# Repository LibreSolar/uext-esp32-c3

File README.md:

# WiFi/Bluetooth communication board based on ESP32-C3 for UEXT connector

 First boards tested, some issues might still be open.

Schematic: [PDF file](build/uext-esp32-c3.pdf)

Bill of Materials: [CSV file](build/uext-esp32-c3_bom.csv) or [interactive HTML BOM](https://libre.solar/uext-esp32-c3/build/uext-esp32-c3_ibom.html)

## Features

- UEXT connector to communicate with host MCU via UART
- Flashing via built-in USB port
- Internal power supply for firmware upgrades

## Firmware

This board can be programmed with [Zephyr RTOS](https://docs.zephyrproject.org/latest/) or [ESP-IDF](https://docs.espressif.com/projects/esp-idf/en/latest/esp32c3/get-started/index.html).

## License

The hardware is licensed under the [CERN Open Hardware Licence Version 2 - Weakly Reciprocal](LICENCE).

Documentation is licensed under the [Creative Commons Attribution-ShareAlike 4.0 International (CC BY-SA 4.0) License](https://creativecommons.org/licenses/by-sa/4.0/).

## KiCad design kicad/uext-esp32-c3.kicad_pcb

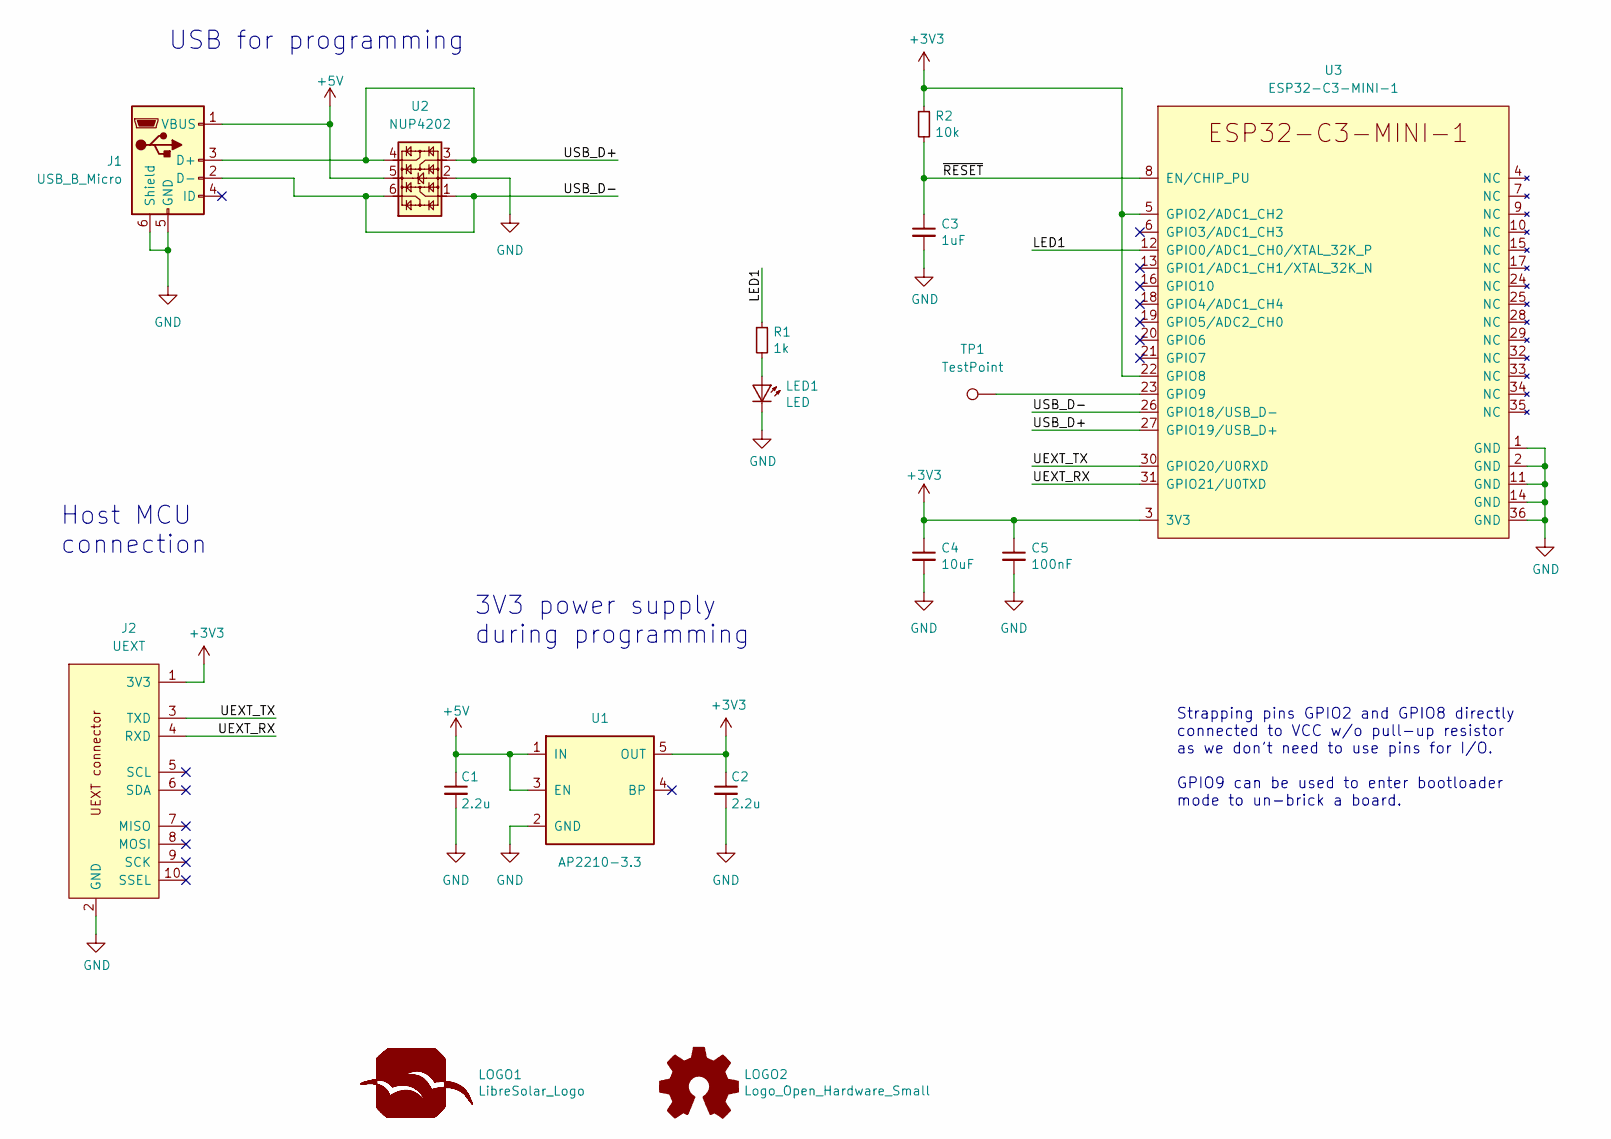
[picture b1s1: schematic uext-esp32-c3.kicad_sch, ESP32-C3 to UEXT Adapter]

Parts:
C1, C2: 2.2u; C_0603_1608
C3: 1uF; C_0603_1608
C4: 10uF; C_0805_2012
C5: 100nF; C_0603_1608
J1: USB_B_Micro; USB_Micro-B_10103594-0001LF; PartNumber 10103594-0001LF
J2: UEXT; PinSocket_2x05_P2.54mm_Vertical
LED1: LED; LED_0603_1608Metric; PartNumber red
LOGO1: LibreSolar_Logo; LIBRESOLAR_LOGO
LOGO2: Logo_Open_Hardware_Small; OSHW-Logo_5.7x6mm_SilkScreen
R1: 1k; R_0603_1608
R2: 10k; R_0603_1608
TP1: TestPoint; TestPoint_Pad_D1.0mm
U1: AP2210-3.3; SOT-23-5; PartNumber AP2210K-3.3TRG1
U2: NUP4202; SOT-363_SC-70-6; PartNumber NUP4202W1T2G
U3: ESP32-C3-MINI-1; PartNumber ESP32-C3-MINI-1-N4

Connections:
+3V3: C2.1, C4.1, C5.1, J2.1 (3V3), R2.1, U1.5 (OUT), U3.3 (3V3), U3.5 (GPIO2/ADC1_CH2), U3.22 (GPIO8)
+5V: C1.1, J1.1 (VBUS), U1.1 (IN), U1.3 (EN), U2.5
/LED1: R1.1, U3.12 (GPIO0/ADC1_CH0/XTAL_32K_P)
/UEXT_RX: J2.4 (RXD), U3.31 (GPIO21/U0TXD)
/UEXT_TX: J2.3 (TXD), U3.30 (GPIO20/U0RXD)
/USB_D+: J1.3 (D+), U2.3, U2.4, U3.27 (GPIO19/USB_D+)
/USB_D-: J1.2 (D-), U2.1, U2.6, U3.26 (GPIO18/USB_D-)
/~RESET: C3.1, R2.2, U3.8 (EN/CHIP_PU)
GND: C1.2, C2.2, C3.2, C4.2, C5.2, J1.5 (GND), J1.6 (Shield), J2.2 (GND), LED1.1 (K), U1.2 (GND), U2.2, U3.1 (GND), U3.2 (GND), U3.11 (GND), U3.14 (GND), U3.36 (GND)
unnamed: LED1.2 (A), R1.2
unnamed: TP1.1, U3.23 (GPIO9)

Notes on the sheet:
3V3 power supply during programming
Host MCU connection
USB for programming
Strapping pins GPIO2 and GPIO8 directly connected to VCC w/o pull-up resistor as we don't need to use pins for I/O. GPIO9 can be used to enter bootloader mode to un-brick a board.

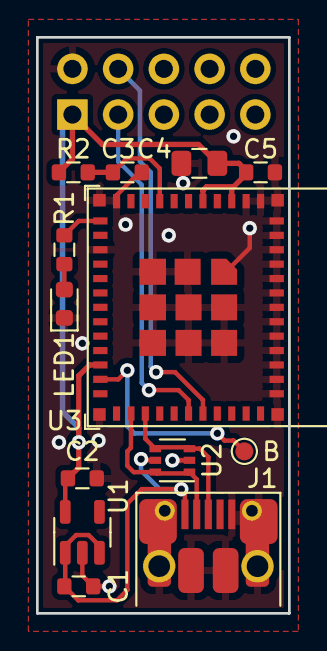
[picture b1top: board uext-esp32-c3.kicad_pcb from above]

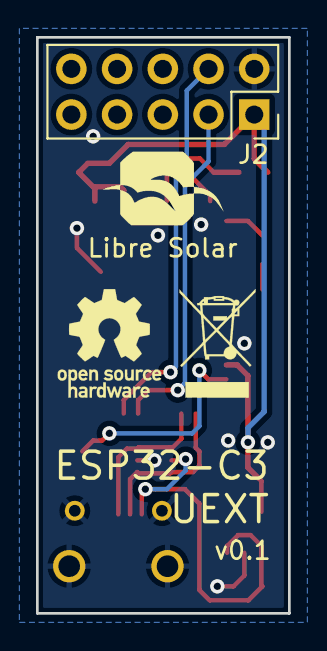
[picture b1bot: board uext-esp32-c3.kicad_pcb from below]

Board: 2 copper layers, 14.0 x 32.0 mm, 16 parts (3 on the bottom side), 11 nets.

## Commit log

2023-02-13 Fix path to interactive BOM

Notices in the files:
kicad/uext-esp32-c3.kicad_sch:
License: Creative Commons Attribution-ShareAlike 4.0 International
